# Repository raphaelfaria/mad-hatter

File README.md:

# Acheron 40-SM-O-MX-TH-WI (Codename "SharkPCB")

Table of Contents
=================

  * [Project overview](#project-overview)
  * [Frequently Asked Questions (FAQ)](#faq)
  * [Board preview](#board-preview-version-31)
  * [Changelog](#changelog-and-version-control)
  * [Bill of Materials](#bill-of-Materials)
  * [Acknowledgements](#Acknowledgements)
  * [License](#license)

## Project overview

The Mad Hatter is a freely available, open-source ergo keyboard Printed Circuit Board (PCB), designed to be compatible with TGR Alice plates and cases. All resources and software used to design this board are open-source and/or freely available.

Here's a list of the board's features:

- AVR ATMEGA32U4 processor;

- Kailh hotswap sockets

- QMK firmware compatible;

- USB mini connector;

Additionally, plate gerber files are also available so that the user can order them made from the same manufacturer as the PCBs and out of the same material (FR4, a fiberglass enhanced resin laminate). This makes production cheaper and faster.

## FAQ 

<!-------------------------------------------------------------------->

<details><summary> Is this design functional and tested? </summary>

> It's not yet tested. A prototype is soon to be printed for proper testing.

</details>

<!-------------------------------------------------------------------->

<details><summary> How can I obtain this PCB? Is there an IC or a GB thread? </summary>

> Currently it's only DIY. You can order the PCBs from a manufacturer like JLCPCB (for instructions see [this link](https://www.youtube.com/watch?v=0u9Io4pw-b0) starting at 1:02:00) and the components from LCSC (how to do that in [this link](https://www.youtube.com/watch?v=eFgOC5_1VYU&t=176s)) and build the board. This takes some expertise in electronics though, as the SMD parts require knowledge and specialized tools and supplies. This is why me and Steve hold Group Buys. Also manufacturers generally have a Minimum Order Quantity of 5 or 10 PCBs. Feel free to arranje a group buy with your circle of friends.

</details>

<!-------------------------------------------------------------------->

<details><summary> Can anyone contribute to this project? </summary>

> Anyone is welcome to contribute, be it through feature requests, opinions or criticisms. This can be done through the GeekHack posts, issues and questions on GitHub or even through my Discord (#Gondolindrim#9738). If you want to actively contribute to the design, feel free to contact me and we'd be glad to have you. 

</details>

<!-------------------------------------------------------------------->

<details><summary> Why open-source? </summary>

> As I don't intend to profit from this, there is no reason to keep the design closed. I also have the opportunity to contribute to the open-source way of thinking: many heads are better than one. Following these steps I use only open-source stuff to design the keyboards: the ECAD design is made with KiCad, the renders and animations in Blender, the logo design in Inkscape. All these software are run on Arch Linux, which is a Linux distro heavily based on the OSS and KISS principles.

> By adopting free OSS tools any newbie makers can take a look and learn from these designs, that is, I also have an educational reason in mind. In this regard, I also have a transparency principle, that is, anyone in the community can contact me and ask questions about the project and the design decisions or the design process. Any maker can also check my designs and points its flaws.

> Second, there is also the KISS (Keep It Simple, Stupid!) principle in mind. Since this project is completely un-ambicious, I try to keep it as simple as possible, so that the design and community processes are fluid.

</details>

<!-------------------------------------------------------------------->

<details><summary> And why publish the design under a share-alike non-commercial license? </summary>

> The reason for the license is twofold: first, while I want the design to be open-source, that is, educational and freely available, I think it's not just that someone could just take it, make little adaptations (like changing the logos) and profitting from it when the idea of the project is to have the open-source ideas in mind. It's not about myself -- although of course I have some pride in my designs and like to have credit for them -- but about the project ideals.

> Second, I don't condemn the idea of commercializing my designs, I'd just like to know who is selling it so that I can have a good quality control.

</details>

<!-------------------------------------------------------------------->

<details><summary> What resources and software do you use? </summary>

> All the footprints and symbols are available wither on the KiCad libraries or my MX library, which contains footprints and symbols for some components not available on KiCad.

> The design, footprints and symbols are made through KiCad. The 3D models are obtained in sites where the content is free and widely available like 3D Content Central and GrabCad Community, and to edit them I use FreeCAD.

> The logos were designed in Inkscape. The base image was taken from [this page](https://www.vectorportal.com/StockVectors/Animals/SHARK-ILLUSTRATION/15844.aspx) (last access: 26 feb, 2019). Although stated in the Vector Portal site that the designs are freely available to be used in commercially, I tried to contact the uploader, who goes by the name of "Yohan Plantec" with no success.

> The renders and animations are made in Blender.

</details>

<!-------------------------------------------------------------------->

<details><summary> How can I follow your design process and learn from this project? </summary>

> I try to stream the design process when I can. I generally do it at tuesdays and thursdays at 3PM PST (8PM BRT). In the streams I answer general electronics questions, and show how the board is designed. I stream at my [Twitch channel](http://twitch.tv/gondolindrim_). The past streams can be seen in my Youtube channel.

</details>

## Board preview

TBD

## Changelog and version control

TBD

## Bill of Materials

TBD

## Acknowledgements

TBD

## License

This project is licensed under the Creative Commons Non-Commercial Share-Alike 4.0 license, available in (https://creativecommons.org/licenses/by-nc-sa/4.0/).

To know more about why I published the project under this license, please look at the [FAQ section](#faq).

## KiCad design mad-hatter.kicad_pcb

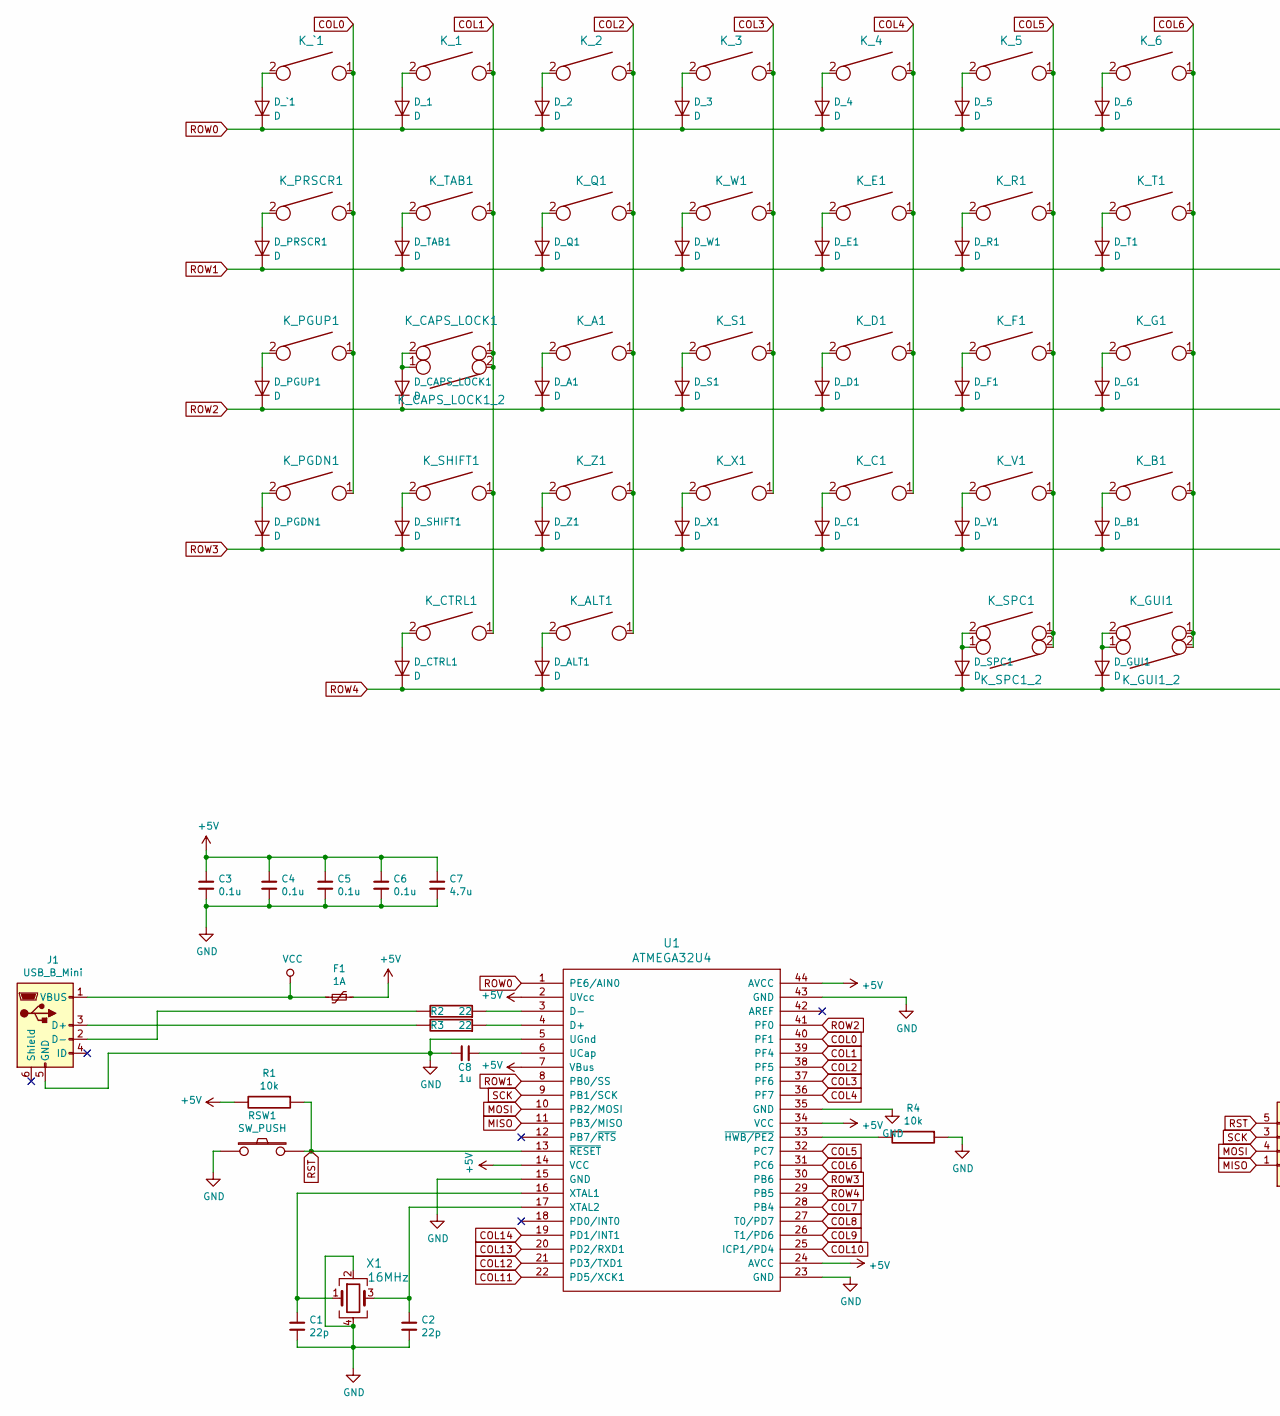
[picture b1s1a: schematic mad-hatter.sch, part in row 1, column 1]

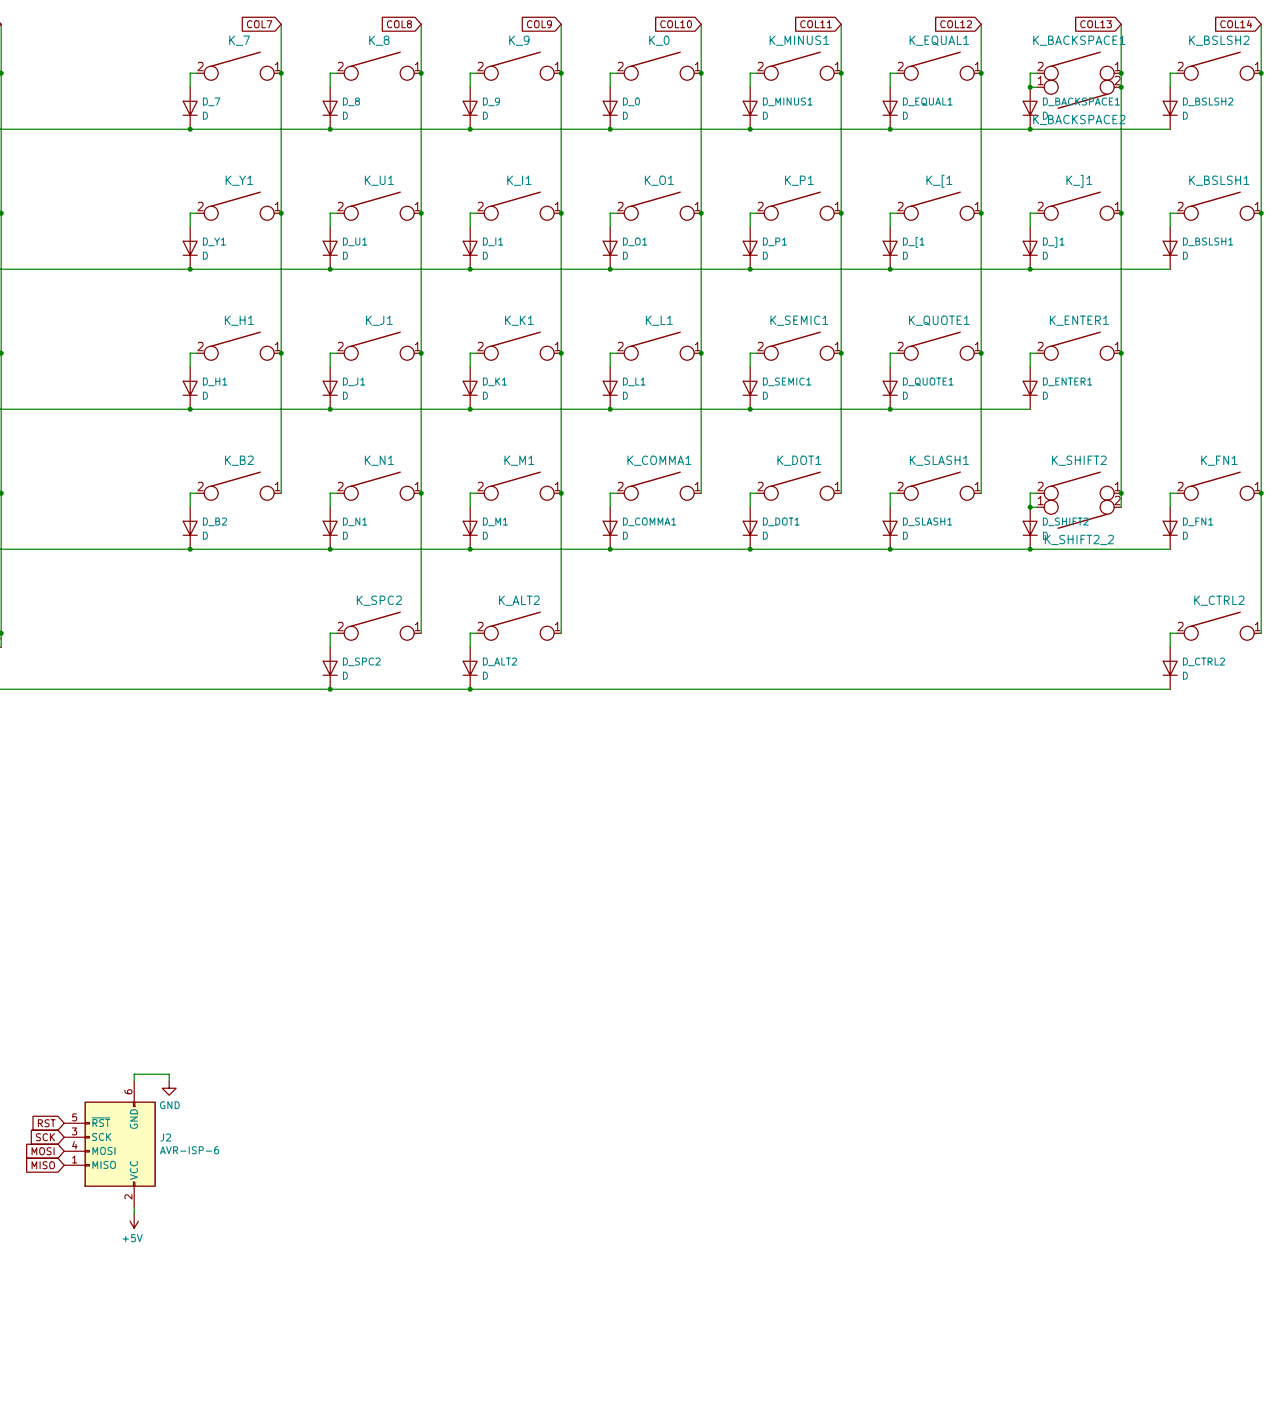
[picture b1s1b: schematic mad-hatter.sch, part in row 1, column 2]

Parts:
C1, C2: 22p; C_0805_2012Metric_Pad1.15x1.40mm_HandSolder
C3, C4, C5, C6: 0.1u; C_0805_2012Metric_Pad1.15x1.40mm_HandSolder
C7: 4.7u; C_0805_2012Metric_Pad1.15x1.40mm_HandSolder
C8: 1u; C_0805_2012Metric_Pad1.15x1.40mm_HandSolder
D_0, D_1, D_2, D_3, D_4, D_5, D_6, D_7, D_8, D_9: D; D_SOD-123
D_A1: D; D_SOD-123
D_ALT1, D_ALT2: D; D_SOD-123
D_B1, D_B2: D; D_SOD-123
D_BACKSPACE1: D; D_SOD-123
D_BSLSH1, D_BSLSH2: D; D_SOD-123
D_C1: D; D_SOD-123
D_CAPS_LOCK1: D; D_SOD-123
D_COMMA1: D; D_SOD-123
D_CTRL1, D_CTRL2: D; D_SOD-123
D_D1: D; D_SOD-123
D_DOT1: D; D_SOD-123
D_E1: D; D_SOD-123
D_ENTER1: D; D_SOD-123
D_EQUAL1: D; D_SOD-123
D_F1: D; D_SOD-123
D_FN1: D; D_SOD-123
D_G1: D; D_SOD-123
D_GUI1: D; D_SOD-123
D_H1: D; D_SOD-123
D_I1: D; D_SOD-123
D_J1: D; D_SOD-123
D_K1: D; D_SOD-123
D_L1: D; D_SOD-123
D_M1: D; D_SOD-123
D_MINUS1: D; D_SOD-123
D_N1: D; D_SOD-123
D_O1: D; D_SOD-123
D_P1: D; D_SOD-123
D_PGDN1: D; D_SOD-123
D_PGUP1: D; D_SOD-123
D_PRSCR1: D; D_SOD-123
D_Q1: D; D_SOD-123
D_QUOTE1: D; D_SOD-123
D_R1: D; D_SOD-123
D_S1: D; D_SOD-123
D_SEMIC1: D; D_SOD-123
D_SHIFT1, D_SHIFT2: D; D_SOD-123
D_SLASH1: D; D_SOD-123
D_SPC1, D_SPC2: D; D_SOD-123
D_T1: D; D_SOD-123
D_TAB1: D; D_SOD-123
D_U1: D; D_SOD-123
D_V1: D; D_SOD-123
D_W1: D; D_SOD-123
D_X1: D; D_SOD-123
D_Y1: D; D_SOD-123
D_Z1: D; D_SOD-123
D_[1: D; D_SOD-123
D_]1: D; D_SOD-123
D_`1: D; D_SOD-123
F1: 1A; Fuse_1206_3216Metric_Pad1.42x1.75mm_HandSolder
J1: USB_B_Mini; miniB_connector
J2: AVR-ISP-6; AVR_ICSP_3x2
K_0, K_1, K_2, K_3, K_4, K_5, K_6, K_7, K_8, K_9: KEYSW; MX100H
K_A1: KEYSW; MX100H
K_ALT1, K_ALT2: KEYSW; MX100H
K_B1, K_B2: KEYSW; MX100H
K_BACKSPACE1, K_BACKSPACE2: KEYSW; MX100H
K_BSLSH1, K_BSLSH2: KEYSW; MX100H
K_C1: KEYSW; MX100H
K_CAPS_LOCK1, K_CAPS_LOCK1_2: KEYSW; MX100H
K_COMMA1: KEYSW; MX100H
K_CTRL1, K_CTRL2: KEYSW; MX100H
K_D1: KEYSW; MX100H
K_DOT1: KEYSW; MX100H
K_E1: KEYSW; MX100H
K_ENTER1: KEYSW; MX100H
K_EQUAL1: KEYSW; MX100H
K_F1: KEYSW; MX100H
K_FN1: KEYSW; MX100H
K_G1: KEYSW; MX100H
K_GUI1, K_GUI1_2: KEYSW; MX100H
K_H1: KEYSW; MX100H
K_I1: KEYSW; MX100H
K_J1: KEYSW; MX100H
K_K1: KEYSW; MX100H
K_L1: KEYSW; MX100H
K_M1: KEYSW; MX100H
K_MINUS1: KEYSW; MX100H
K_N1: KEYSW; MX100H
K_O1: KEYSW; MX100H
K_P1: KEYSW; MX100H
K_PGDN1: KEYSW; MX100H
K_PGUP1: KEYSW; MX100H
K_PRSCR1: KEYSW; MX100H
K_Q1: KEYSW; MX100H
K_QUOTE1: KEYSW; MX100H
K_R1: KEYSW; MX100H
K_S1: KEYSW; MX100H
K_SEMIC1: KEYSW; MX100H
K_SHIFT1, K_SHIFT2, K_SHIFT2_2: KEYSW; MX100H
K_SLASH1: KEYSW; MX100H
K_SPC1, K_SPC1_2, K_SPC2: KEYSW; MX100H
K_T1: KEYSW; MX100H
K_TAB1: KEYSW; MX100H
K_U1: KEYSW; MX100H
K_V1: KEYSW; MX100H
K_W1: KEYSW; MX100H
K_X1: KEYSW; MX100H
K_Y1: KEYSW; MX100H
K_Z1: KEYSW; MX100H
K_[1: KEYSW; MX100H
K_]1: KEYSW; MX100H
K_`1: KEYSW; MX100H
R1, R4: 10k; R_0805_2012Metric_Pad1.15x1.40mm_HandSolder
R2, R3: 22; R_0805_2012Metric_Pad1.15x1.40mm_HandSolder
RSW1: SW_PUSH; smdPushBtn
U1: ATMEGA32U4; QFP44_reflow
X1: 16MHz; Crystal_SMD_3225-4Pin_3.2x2.5mm

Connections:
+5V: C3.1, C4.1, C5.1, C6.1, C7.1, F1.1, J2.2 (VCC), R1.2, U1.2 (UVcc), U1.7 (VBus), U1.14 (VCC), U1.24 (AVCC), U1.34 (VCC), U1.44 (AVCC); also elsewhere on the board
COL0: K_PGDN1.1, K_PGUP1.1, K_PRSCR1.1, K_`1.1, U1.40 (PF1)
COL1: K_1.1, K_CAPS_LOCK1.1, K_CAPS_LOCK1_2.2, K_CTRL1.1, K_SHIFT1.1, K_TAB1.1, U1.39 (PF4)
COL2: K_2.1, K_A1.1, K_ALT1.1, K_Q1.1, K_Z1.1, U1.38 (PF5)
COL3: K_3.1, K_S1.1, K_W1.1, K_X1.1, U1.37 (PF6)
COL4: K_4.1, K_C1.1, K_D1.1, K_E1.1, U1.36 (PF7)
COL5: K_5.1, K_F1.1, K_R1.1, K_SPC1.1, K_SPC1_2.2, K_V1.1, U1.32 (PC7)
COL6: K_6.1, K_B1.1, K_G1.1, K_GUI1.1, K_GUI1_2.2, K_T1.1, U1.31 (PC6)
COL7: K_7.1, K_B2.1, K_H1.1, K_Y1.1, U1.28 (PB4)
COL8: K_8.1, K_J1.1, K_N1.1, K_SPC2.1, K_U1.1, U1.27 (T0/PD7)
COL9: K_9.1, K_ALT2.1, K_I1.1, K_K1.1, K_M1.1, U1.26 (T1/PD6)
COL10: K_0.1, K_COMMA1.1, K_L1.1, K_O1.1, U1.25 (ICP1/PD4)
COL11: K_DOT1.1, K_MINUS1.1, K_P1.1, K_SEMIC1.1, U1.22 (PD5/XCK1)
COL12: K_EQUAL1.1, K_QUOTE1.1, K_SLASH1.1, K_[1.1, U1.21 (PD3/TXD1)
COL13: K_BACKSPACE1.1, K_BACKSPACE2.2, K_ENTER1.1, K_SHIFT2.1, K_SHIFT2_2.2, K_]1.1, U1.20 (PD2/RXD1)
COL14: K_BSLSH1.1, K_BSLSH2.1, K_CTRL2.1, K_FN1.1, U1.19 (PD1/INT1)
GND: C1.2, C2.2, C3.2, C4.2, C5.2, C6.2, C7.2, C8.2, J1.5 (GND), J2.6 (GND), R4.1, RSW1.1, U1.5 (UGnd), U1.15 (GND), U1.23 (GND), U1.35 (GND), U1.43 (GND), X1.2, X1.4; also elsewhere on the board
MISO: J2.1 (MISO), U1.11 (PB3/MISO); also elsewhere on the board
MOSI: J2.4 (MOSI), U1.10 (PB2/MOSI); also elsewhere on the board
unnamed: C1.1, U1.16 (XTAL1), X1.1
unnamed: C2.1, U1.17 (XTAL2), X1.3
unnamed: C8.1, U1.6 (UCap)
unnamed: D_0.2 (A), K_0.2
unnamed: D_1.2 (A), K_1.2
unnamed: D_2.2 (A), K_2.2
unnamed: D_3.2 (A), K_3.2
unnamed: D_4.2 (A), K_4.2
unnamed: D_5.2 (A), K_5.2
unnamed: D_6.2 (A), K_6.2
unnamed: D_7.2 (A), K_7.2
unnamed: D_8.2 (A), K_8.2
unnamed: D_9.2 (A), K_9.2
unnamed: D_A1.2 (A), K_A1.2
unnamed: D_ALT1.2 (A), K_ALT1.2
unnamed: D_ALT2.2 (A), K_ALT2.2
unnamed: D_B1.2 (A), K_B1.2
unnamed: D_B2.2 (A), K_B2.2
unnamed: D_BACKSPACE1.2 (A), K_BACKSPACE1.2, K_BACKSPACE2.1
unnamed: D_BSLSH1.2 (A), K_BSLSH1.2
unnamed: D_BSLSH2.2 (A), K_BSLSH2.2
unnamed: D_C1.2 (A), K_C1.2
unnamed: D_CAPS_LOCK1.2 (A), K_CAPS_LOCK1.2, K_CAPS_LOCK1_2.1
unnamed: D_COMMA1.2 (A), K_COMMA1.2
unnamed: D_CTRL1.2 (A), K_CTRL1.2
unnamed: D_CTRL2.2 (A), K_CTRL2.2
unnamed: D_D1.2 (A), K_D1.2
unnamed: D_DOT1.2 (A), K_DOT1.2
unnamed: D_E1.2 (A), K_E1.2
unnamed: D_ENTER1.2 (A), K_ENTER1.2
unnamed: D_EQUAL1.2 (A), K_EQUAL1.2
unnamed: D_F1.2 (A), K_F1.2
unnamed: D_FN1.2 (A), K_FN1.2
unnamed: D_G1.2 (A), K_G1.2
unnamed: D_GUI1.2 (A), K_GUI1.2, K_GUI1_2.1
unnamed: D_H1.2 (A), K_H1.2
unnamed: D_I1.2 (A), K_I1.2
unnamed: D_J1.2 (A), K_J1.2
unnamed: D_K1.2 (A), K_K1.2
unnamed: D_L1.2 (A), K_L1.2
unnamed: D_M1.2 (A), K_M1.2
unnamed: D_MINUS1.2 (A), K_MINUS1.2
unnamed: D_N1.2 (A), K_N1.2
unnamed: D_O1.2 (A), K_O1.2
unnamed: D_P1.2 (A), K_P1.2
unnamed: D_PGDN1.2 (A), K_PGDN1.2
unnamed: D_PGUP1.2 (A), K_PGUP1.2
unnamed: D_PRSCR1.2 (A), K_PRSCR1.2
unnamed: D_Q1.2 (A), K_Q1.2
unnamed: D_QUOTE1.2 (A), K_QUOTE1.2
unnamed: D_R1.2 (A), K_R1.2
unnamed: D_S1.2 (A), K_S1.2
unnamed: D_SEMIC1.2 (A), K_SEMIC1.2
unnamed: D_SHIFT1.2 (A), K_SHIFT1.2
unnamed: D_SHIFT2.2 (A), K_SHIFT2.2, K_SHIFT2_2.1
unnamed: D_SLASH1.2 (A), K_SLASH1.2
unnamed: D_SPC1.2 (A), K_SPC1.2, K_SPC1_2.1
unnamed: D_SPC2.2 (A), K_SPC2.2
unnamed: D_T1.2 (A), K_T1.2
unnamed: D_TAB1.2 (A), K_TAB1.2
unnamed: D_U1.2 (A), K_U1.2
unnamed: D_V1.2 (A), K_V1.2
unnamed: D_W1.2 (A), K_W1.2
unnamed: D_X1.2 (A), K_X1.2
unnamed: D_Y1.2 (A), K_Y1.2
unnamed: D_Z1.2 (A), K_Z1.2
unnamed: D_[1.2 (A), K_[1.2
unnamed: D_]1.2 (A), K_]1.2
unnamed: D_`1.2 (A), K_`1.2
unnamed: J1.2 (D-), R2.2
unnamed: J1.3 (D+), R3.2
unnamed: R2.1, U1.3 (D-)
unnamed: R3.1, U1.4 (D+)
unnamed: R4.2, U1.33 (~HWB/PE2)
ROW0: D_0.1 (K), D_1.1 (K), D_2.1 (K), D_3.1 (K), D_4.1 (K), D_5.1 (K), D_6.1 (K), D_7.1 (K), D_8.1 (K), D_9.1 (K), D_BACKSPACE1.1 (K), D_BSLSH2.1 (K), D_EQUAL1.1 (K), D_MINUS1.1 (K), D_`1.1 (K), U1.1 (PE6/AIN0)
ROW1: D_BSLSH1.1 (K), D_E1.1 (K), D_I1.1 (K), D_O1.1 (K), D_P1.1 (K), D_PRSCR1.1 (K), D_Q1.1 (K), D_R1.1 (K), D_T1.1 (K), D_TAB1.1 (K), D_U1.1 (K), D_W1.1 (K), D_Y1.1 (K), D_[1.1 (K), D_]1.1 (K), U1.8 (PB0/SS)
ROW2: D_A1.1 (K), D_CAPS_LOCK1.1 (K), D_D1.1 (K), D_ENTER1.1 (K), D_F1.1 (K), D_G1.1 (K), D_H1.1 (K), D_J1.1 (K), D_K1.1 (K), D_L1.1 (K), D_PGUP1.1 (K), D_QUOTE1.1 (K), D_S1.1 (K), D_SEMIC1.1 (K), U1.41 (PF0)
ROW3: D_B1.1 (K), D_B2.1 (K), D_C1.1 (K), D_COMMA1.1 (K), D_DOT1.1 (K), D_FN1.1 (K), D_M1.1 (K), D_N1.1 (K), D_PGDN1.1 (K), D_SHIFT1.1 (K), D_SHIFT2.1 (K), D_SLASH1.1 (K), D_V1.1 (K), D_X1.1 (K), D_Z1.1 (K), U1.30 (PB6)
ROW4: D_ALT1.1 (K), D_ALT2.1 (K), D_CTRL1.1 (K), D_CTRL2.1 (K), D_GUI1.1 (K), D_SPC1.1 (K), D_SPC2.1 (K), U1.29 (PB5)
RST: J2.5 (~RST), R1.1, RSW1.2, U1.13 (~RESET); also elsewhere on the board
SCK: J2.3 (SCK), U1.9 (PB1/SCK); also elsewhere on the board
VCC: F1.2, J1.1 (VBUS)

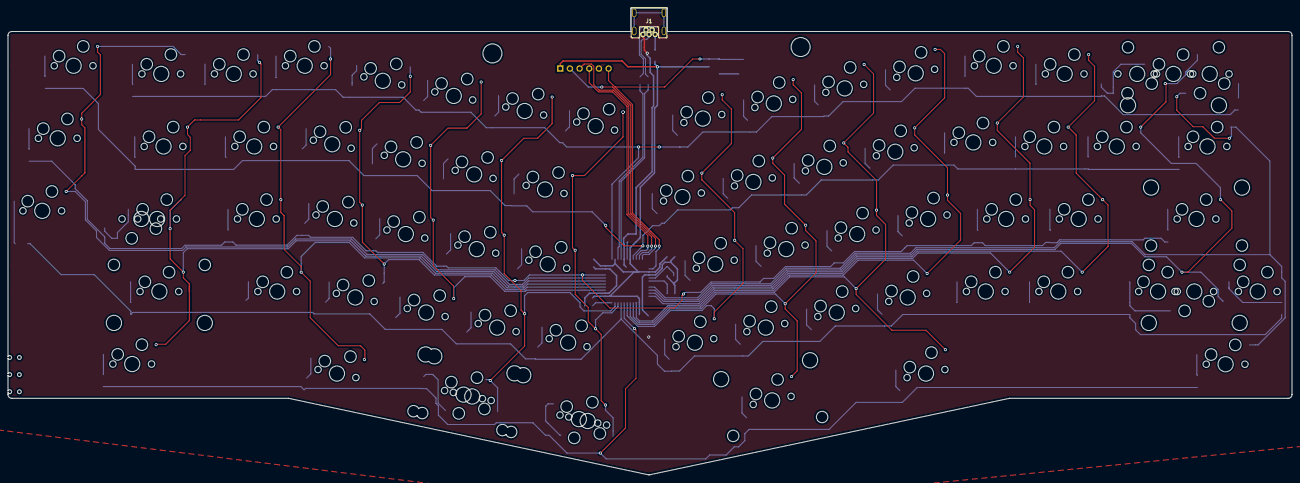
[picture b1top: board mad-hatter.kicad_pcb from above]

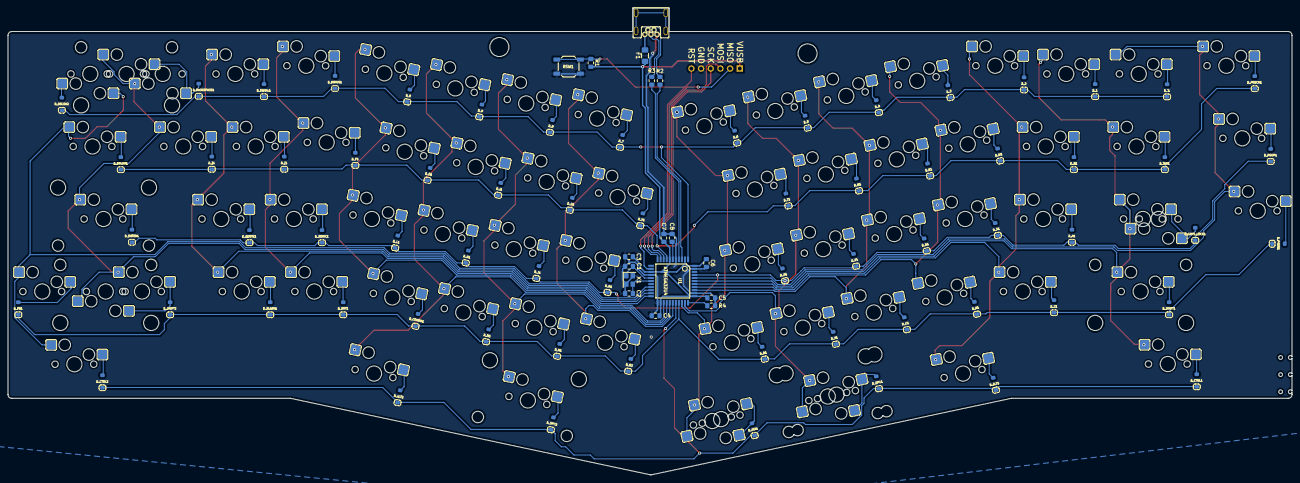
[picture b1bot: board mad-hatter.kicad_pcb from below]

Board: 2 copper layers, 337.2 x 122.6 mm, 160 parts (153 on the bottom side), 101 nets.

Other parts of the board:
P?: CONN_1; PIN_1
P?#2, P?#3, P?#4, P?#6: CONN_1; PIN_1
P?#5: CONN_1; PIN_1_SQUARE

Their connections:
+5V: P?#5.1; also elsewhere on the board
GND: P?#2.5; also elsewhere on the board
MISO: P?#6.2; also elsewhere on the board
MOSI: P?#4.3; also elsewhere on the board
RST: P?.6; also elsewhere on the board
SCK: P?#3.4; also elsewhere on the board

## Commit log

2019-03-19 Main tracing complete
2019-03-19 Finished tracing
2019-03-19 Starts tracing
2019-03-19 Create LICENSE
2019-03-19 Fixes crystal connection; improves matrix; adds fuse
2019-03-19 Convert IC to TQFP
2019-03-19 Renaming: Mad Hatter
2019-03-19 Improvements
2019-03-19 Starts adding ISP pads
2019-03-19 Adds gitignore
2019-03-20 Quick README update
2019-03-22 Various fixes:
    - changes footprints to acheron
    - routing fixes
    - reorder ISP pins
2019-03-30 Some more improvements
2019-04-13 Inverts ISP connector; small fixes
2019-04-22 Improves placement of crystal
2019-04-22 Reorganize capacitors
2019-04-25 Improves caps placement
2019-05-27 Small fixes
